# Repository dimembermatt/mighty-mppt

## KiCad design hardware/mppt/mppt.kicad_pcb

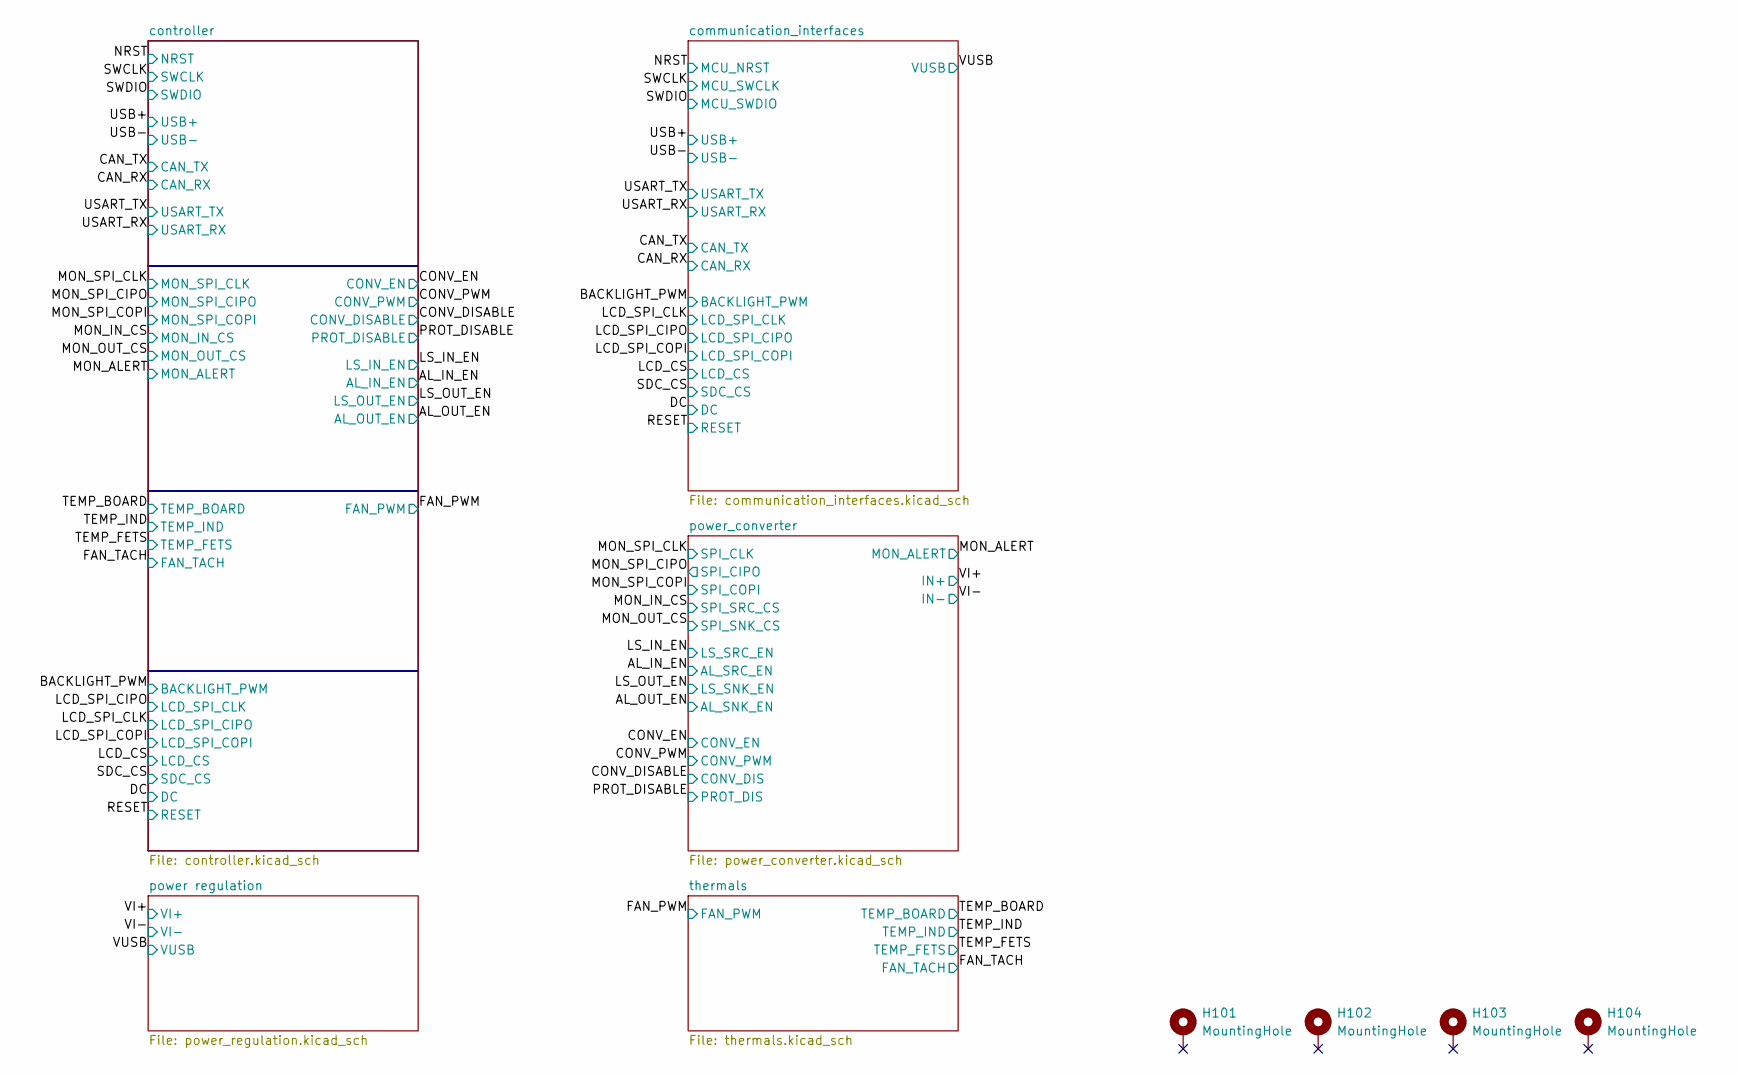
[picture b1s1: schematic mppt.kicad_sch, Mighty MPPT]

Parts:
H101, H102, H103, H104: MountingHole; MountingHole_2.7mm_M2.5_DIN965_Pad_TopBottom

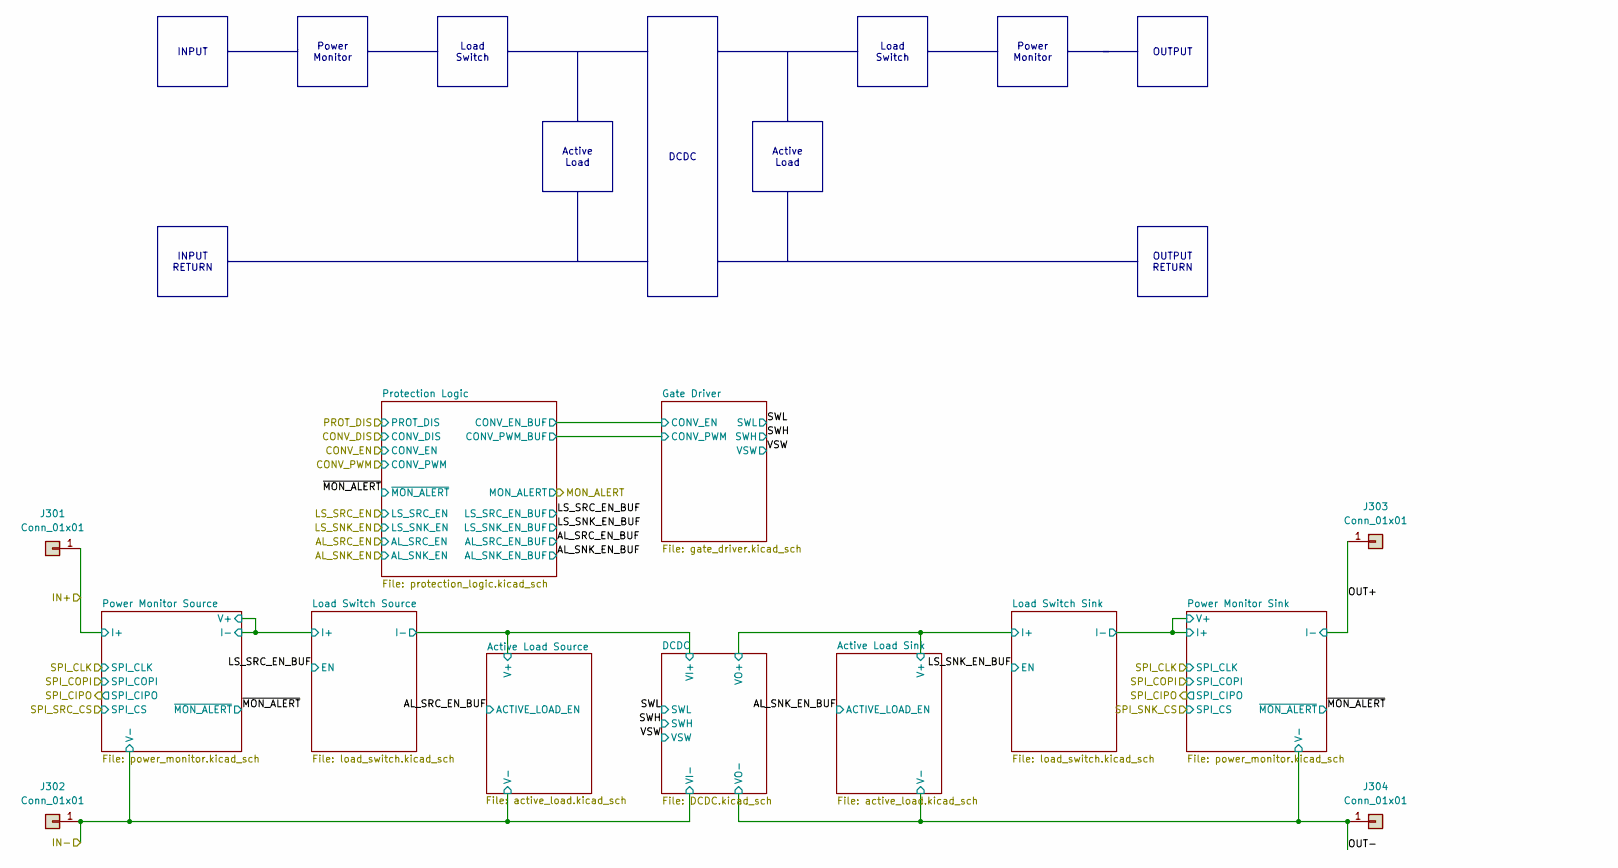
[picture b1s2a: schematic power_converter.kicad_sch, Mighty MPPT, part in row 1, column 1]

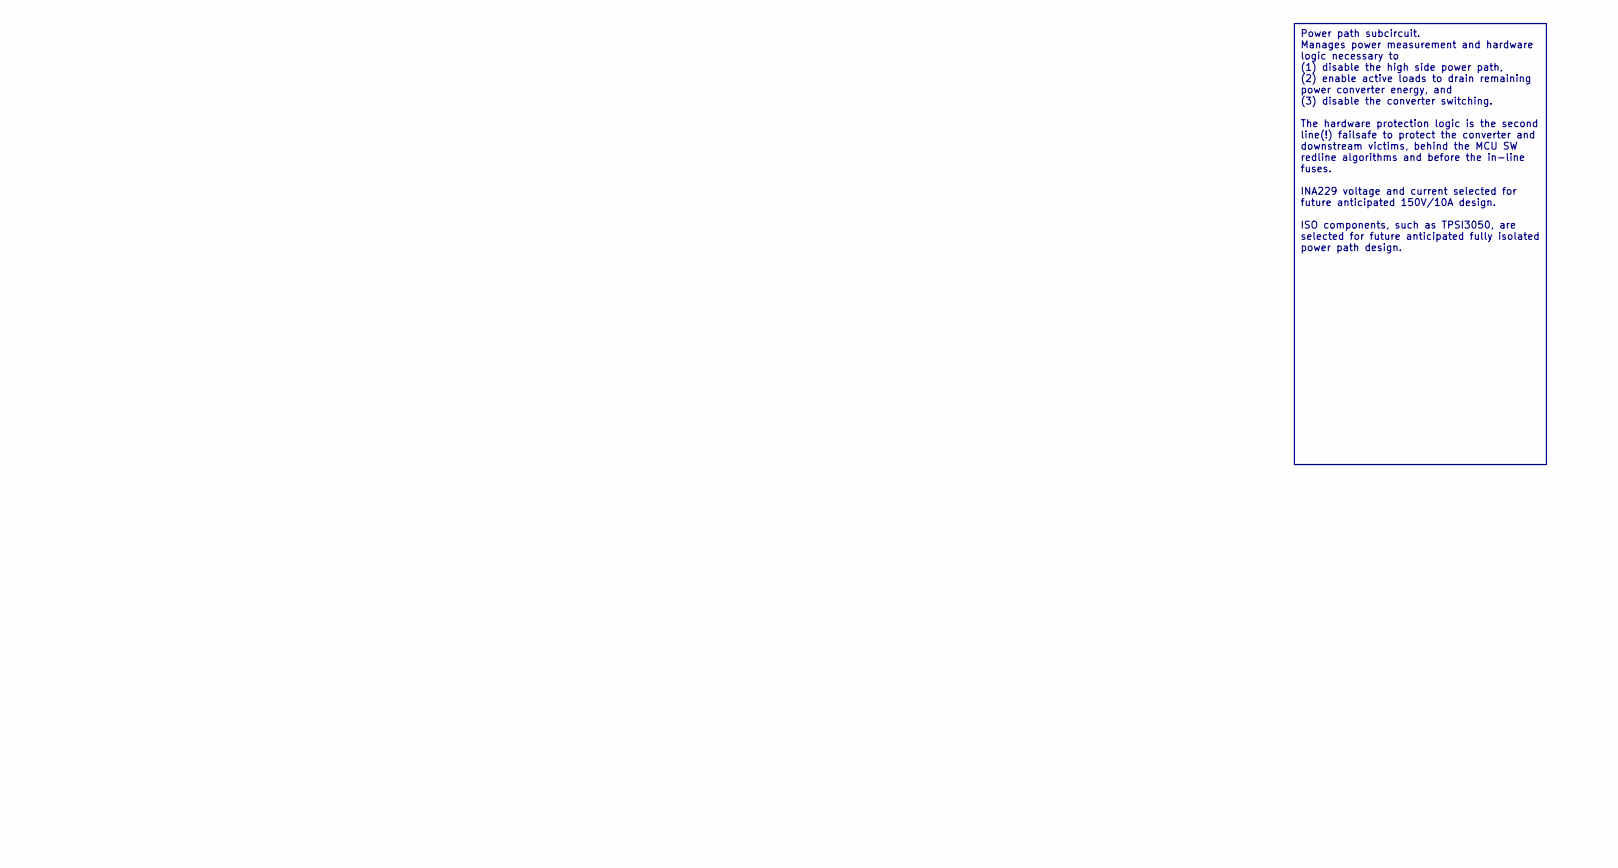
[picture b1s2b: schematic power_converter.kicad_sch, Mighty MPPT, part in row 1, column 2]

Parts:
J301, J302, J303, J304: Conn_01x01; ke_7771_SEMS

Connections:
/VI+: J301.1; also elsewhere on the board
/VI-: J302.1; also elsewhere on the board
/power_converter/OUT+: J303.1; also elsewhere on the board
/power_converter/OUT-: J304.1; also elsewhere on the board

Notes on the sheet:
INPUT
OUTPUT
Power Monitor
OUTPUT RETURN
DCDC
Power Monitor
Power path subcircuit. Manages power measurement and hardware logic necessary to (1) disable the high side power path, (2) enable active loads to drain remaining power converter energy, and (3) disable the converter switching. The hardware protection logic is the second line(!) failsafe to protect 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
Active Load
INPUT RETURN
Load Switch

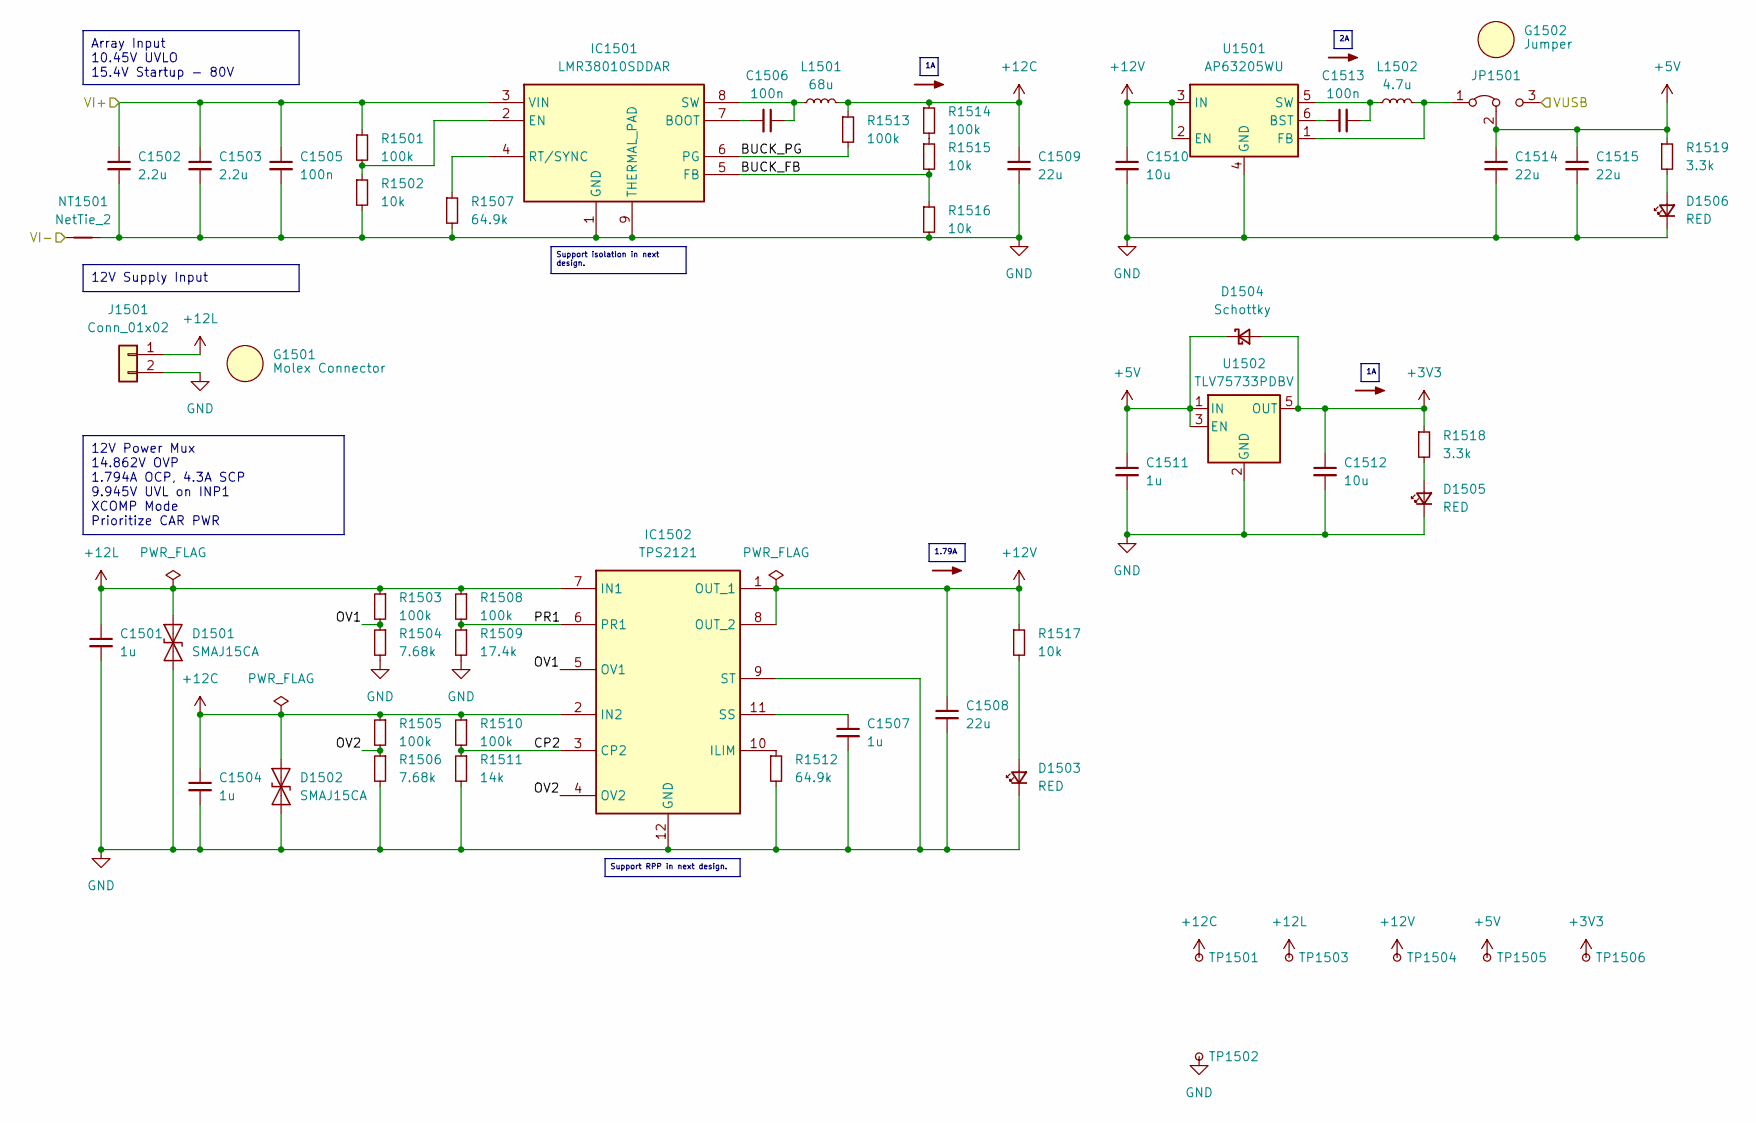
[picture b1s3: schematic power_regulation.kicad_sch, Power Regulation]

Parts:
C1501, C1504, C1507, C1511: 1u; C_0603_1608Metric_Pad1.08x0.95mm_HandSolder
C1502, C1503: 2.2u; C_2220_5750Metric
C1505: 100n; C_0805_2012Metric
C1506, C1513: 100n; C_0402_1005Metric_Pad0.74x0.62mm_HandSolder
C1508, C1509, C1514, C1515: 22u; C_1206_3216Metric
C1510, C1512: 10u; C_1206_3216Metric_Pad1.33x1.80mm_HandSolder
D1501, D1502: SMAJ15CA; D_SMA
D1503, D1505, D1506: RED; LED_0805_2012Metric_Pad1.15x1.40mm_HandSolder
D1504: Schottky; D_SOD-123F
G1501: Molex Connector
G1502: Jumper
IC1501: LMR38010SDDAR; ti_LMR38010_SDDAR
IC1502: TPS2121; ti_TPS2121_RUXR
J1501: Conn_01x02; Molex_Micro-Fit_3.0_43650-0215_1x02_P3.00mm_Vertical
JP1501: Jumper_3_Bridged12; PinSocket_1x03_P2.54mm_Vertical
L1501: 68u; L_Bourns_SRN6045TA
L1502: 4.7u; L_Bourns_SRN6045TA
NT1501: NetTie_2; NetTie-2_SMD_Pad2.0mm
R1501, R1503, R1505, R1508, R1510, R1513, R1514: 100k; R_0603_1608Metric_Pad0.98x0.95mm_HandSolder
R1502, R1515, R1516, R1517: 10k; R_0603_1608Metric_Pad0.98x0.95mm_HandSolder
R1504, R1506: 7.68k; R_0603_1608Metric_Pad0.98x0.95mm_HandSolder
R1507, R1512: 64.9k; R_0603_1608Metric_Pad0.98x0.95mm_HandSolder
R1509: 17.4k; R_0603_1608Metric_Pad0.98x0.95mm_HandSolder
R1511: 14k; R_0603_1608Metric_Pad0.98x0.95mm_HandSolder
R1518, R1519: 3.3k; R_0603_1608Metric_Pad0.98x0.95mm_HandSolder
TP1501, TP1502, TP1503, TP1504, TP1505, TP1506: TestPoint_Small; TestPoint_Pad_D1.0mm
U1501: AP63205WU; TSOT-23-6
U1502: TLV75733PDBV; SOT-23-5

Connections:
+3V3: C1512.1, D1504.2 (A), R1518.1, TP1506.1, U1502.5 (OUT); also elsewhere on the board
+5V: C1511.1, C1514.1, C1515.1, D1504.1 (K), JP1501.2 (C), R1519.1, TP1505.1, U1502.1 (IN), U1502.3 (EN); also elsewhere on the board
+12C: C1504.1, C1509.1, D1502.2 (A2), IC1502.2 (IN2), L1501.2, R1505.1, R1510.1, R1513.1, R1514.1, TP1501.1
+12L: C1501.1, D1501.2 (A2), IC1502.7 (IN1), J1501.1, R1503.1, R1508.1, TP1503.1
+12V: C1508.1, C1510.1, IC1502.1 (OUT_1), IC1502.8 (OUT_2), R1517.1, TP1504.1, U1501.2 (EN), U1501.3 (IN)
/VI+: C1502.1, C1503.1, C1505.1, IC1501.3 (VIN), R1501.1; also elsewhere on the board
/VI-: NT1501.2; also elsewhere on the board
/VUSB: JP1501.3 (B); also elsewhere on the board
/power regulation/BUCK_FB: IC1501.5 (FB), R1515.2, R1516.1
/power regulation/BUCK_PG: IC1501.6 (PG), R1513.2
/power regulation/CP2: IC1502.3 (CP2), R1510.2, R1511.1
/power regulation/OV1: IC1502.5 (OV1), R1503.2, R1504.1
/power regulation/OV2: IC1502.4 (OV2), R1505.2, R1506.1
/power regulation/PR1: IC1502.6 (PR1), R1508.2, R1509.1
GND: C1501.2, C1502.2, C1503.2, C1504.2, C1505.2, C1507.2, C1508.2, C1509.2, C1510.2, C1511.2, C1512.2, C1514.2, C1515.2, D1501.1 (A1), D1502.1 (A1), D1503.1 (K), D1505.1 (K), D1506.1 (K), IC1501.1 (GND), IC1501.9 (THERMAL_PAD), IC1502.9 (ST), IC1502.12 (GND), J1501.2, NT1501.1, R1502.2, R1504.2, R1506.2, R1507.2, R1509.2, R1511.2, R1512.2, R1516.2, TP1502.1, U1501.4 (GND), U1502.2 (GND); also elsewhere on the board
unnamed: D1503.2 (A), R1517.2
unnamed: D1505.2 (A), R1518.2
unnamed: D1506.2 (A), R1519.2
unnamed: C1506.2, IC1501.7 (BOOT)
unnamed: IC1501.2 (EN), R1501.2, R1502.1
unnamed: IC1501.4 (RT/SYNC), R1507.1
unnamed: C1506.1, IC1501.8 (SW), L1501.1
unnamed: IC1502.10 (ILIM), R1512.1
unnamed: C1507.1, IC1502.11 (SS)
unnamed: JP1501.1 (A), L1502.2, U1501.1 (FB)
unnamed: R1514.2, R1515.1
unnamed: C1513.1, U1501.6 (BST)
unnamed: C1513.2, L1502.1, U1501.5 (SW)

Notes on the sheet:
1.79A
Support isolation in next design.
12V Supply Input
12V Power Mux 14.862V OVP 1.794A OCP, 4.3A SCP 9.945V UVL on INP1 XCOMP Mode Prioritize CAR PWR
Array Input 10.45V UVLO 15.4V Startup - 80V
Support RPP in next design.

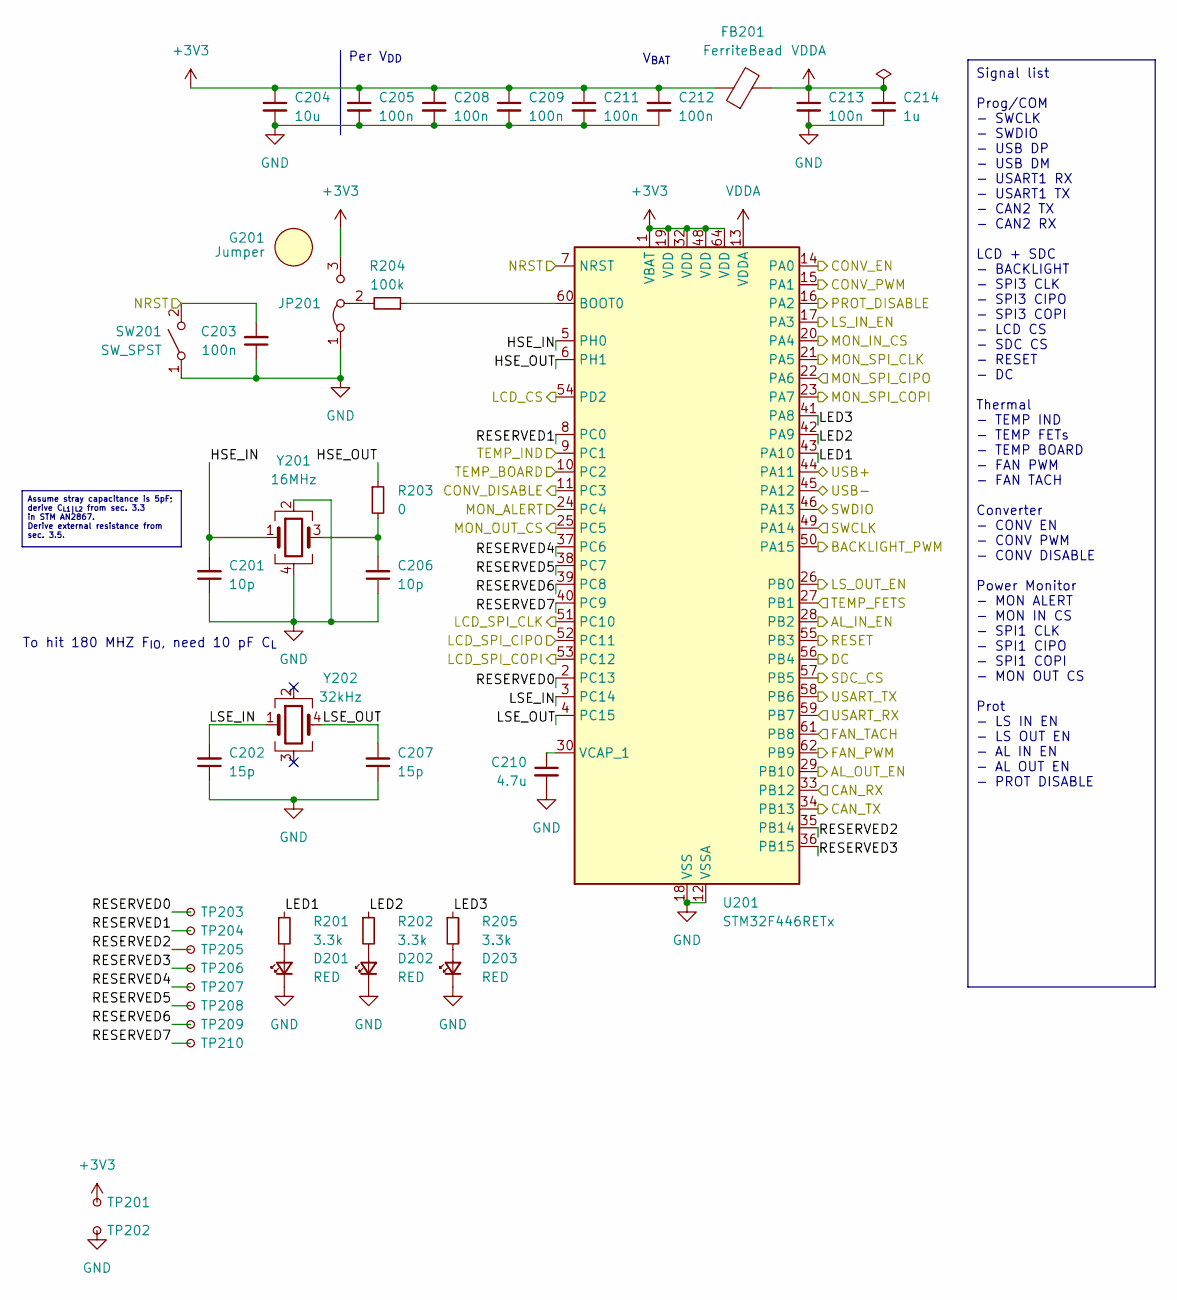
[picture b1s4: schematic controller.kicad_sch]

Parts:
C201, C206: 10p; C_0402_1005Metric
C202, C207: 15p; C_0402_1005Metric
C203, C205, C208, C209, C211, C212, C213: 100n; C_0402_1005Metric_Pad0.74x0.62mm_HandSolder
C204: 10u; C_1206_3216Metric_Pad1.33x1.80mm_HandSolder
C210: 4.7u; C_0603_1608Metric
C214: 1u; C_0603_1608Metric_Pad1.08x0.95mm_HandSolder
D201, D202, D203: RED; LED_0805_2012Metric_Pad1.15x1.40mm_HandSolder
FB201: FerriteBead; R_0603_1608Metric_Pad0.98x0.95mm_HandSolder
G201: Jumper
JP201: Jumper_3_Bridged12; PinSocket_1x03_P2.54mm_Vertical
R201, R202, R205: 3.3k; R_0603_1608Metric_Pad0.98x0.95mm_HandSolder
R203: 0; R_0805_2012Metric_Pad1.20x1.40mm_HandSolder
R204: 100k; R_0603_1608Metric_Pad0.98x0.95mm_HandSolder
SW201: SW_SPST; SW_PUSH_6mm
TP201, TP202, TP203, TP204, TP205, TP206, TP207, TP208, TP209, TP210: TestPoint_Small; TestPoint_Pad_D1.0mm
U201: STM32F446RETx; LQFP-64_10x10mm_P0.5mm
Y201: 16MHz; Crystal_SMD_Abracon_ABM8G-4Pin_3.2x2.5mm
Y202: 32kHz; Crystal_SMD_Abracon_ABS25-4Pin_8.0x3.8mm

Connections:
+3V3: C204.1, C205.1, C208.1, C209.1, C211.1, C212.1, FB201.1, JP201.3 (B), TP201.1, U201.1 (VBAT), U201.19 (VDD), U201.32 (VDD), U201.48 (VDD), U201.64 (VDD); also elsewhere on the board
/AL_IN_EN: U201.28 (PB2); also elsewhere on the board
/AL_OUT_EN: U201.29 (PB10); also elsewhere on the board
/BACKLIGHT_PWM: U201.50 (PA15); also elsewhere on the board
/CAN_RX: U201.33 (PB12); also elsewhere on the board
/CAN_TX: U201.34 (PB13); also elsewhere on the board
/CONV_DISABLE: U201.11 (PC3); also elsewhere on the board
/CONV_EN: U201.14 (PA0); also elsewhere on the board
/CONV_PWM: U201.15 (PA1); also elsewhere on the board
/DC: U201.56 (PB4); also elsewhere on the board
/FAN_PWM: U201.62 (PB9); also elsewhere on the board
/FAN_TACH: U201.61 (PB8); also elsewhere on the board
/LCD_CS: U201.54 (PD2); also elsewhere on the board
/LCD_SPI_CIPO: U201.51 (PC10); also elsewhere on the board
/LCD_SPI_CLK: U201.52 (PC11); also elsewhere on the board
/LCD_SPI_COPI: U201.53 (PC12); also elsewhere on the board
/LS_IN_EN: U201.17 (PA3); also elsewhere on the board
/LS_OUT_EN: U201.26 (PB0); also elsewhere on the board
/MON_ALERT: U201.24 (PC4); also elsewhere on the board
/MON_IN_CS: U201.20 (PA4); also elsewhere on the board
/MON_OUT_CS: U201.25 (PC5); also elsewhere on the board
/MON_SPI_CIPO: U201.22 (PA6); also elsewhere on the board
/MON_SPI_CLK: U201.21 (PA5); also elsewhere on the board
/MON_SPI_COPI: U201.23 (PA7); also elsewhere on the board
/NRST: C203.2, SW201.2 (B), U201.7 (NRST); also elsewhere on the board
/PROT_DISABLE: U201.16 (PA2); also elsewhere on the board
/RESET: U201.55 (PB3); also elsewhere on the board
/SDC_CS: U201.57 (PB5); also elsewhere on the board
/SWCLK: U201.49 (PA14); also elsewhere on the board
/SWDIO: U201.46 (PA13); also elsewhere on the board
/TEMP_BOARD: U201.10 (PC2); also elsewhere on the board
/TEMP_FETS: U201.27 (PB1); also elsewhere on the board
/TEMP_IND: U201.9 (PC1); also elsewhere on the board
/USART_RX: U201.59 (PB7); also elsewhere on the board
/USART_TX: U201.58 (PB6); also elsewhere on the board
/USB+: U201.44 (PA11); also elsewhere on the board
/USB-: U201.45 (PA12); also elsewhere on the board
/controller/HSE_IN: C201.2, U201.5 (PH0), Y201.1
/controller/HSE_OUT: R203.1, U201.6 (PH1)
/controller/LED1: R201.1, U201.43 (PA10)
/controller/LED2: R202.1, U201.42 (PA9)
/controller/LED3: R205.1, U201.41 (PA8)
/controller/LSE_IN: C202.2, U201.3 (PC14), Y202.1
/controller/LSE_OUT: C207.2, U201.4 (PC15), Y202.4
/controller/RESERVED0: TP203.1, U201.2 (PC13)
/controller/RESERVED1: TP204.1, U201.8 (PC0)
/controller/RESERVED2: TP205.1, U201.35 (PB14)
/controller/RESERVED3: TP206.1, U201.36 (PB15)
/controller/RESERVED4: TP207.1, U201.37 (PC6)
/controller/RESERVED5: TP208.1, U201.38 (PC7)
/controller/RESERVED6: TP209.1, U201.39 (PC8)
/controller/RESERVED7: TP210.1, U201.40 (PC9)
GND: C201.1, C202.1, C203.1, C204.2, C205.2, C206.1, C207.1, C208.2, C209.2, C210.2, C211.2, C212.2, C213.2, C214.2, D201.1 (K), D202.1 (K), D203.1 (K), JP201.1 (A), SW201.1 (A), TP202.1, U201.12 (VSSA), U201.18 (VSS), U201.31 (VSS), U201.47 (VSS), U201.63 (VSS), Y201.2, Y201.4; also elsewhere on the board
unnamed: C206.2, R203.2, Y201.3
unnamed: D201.2 (A), R201.2
unnamed: D202.2 (A), R202.2
unnamed: D203.2 (A), R205.2
unnamed: JP201.2 (C), R204.2
unnamed: R204.1, U201.60 (BOOT0)
unnamed: C210.1, U201.30 (VCAP_1)
VDDA: C213.1, C214.1, FB201.2, U201.13 (VDDA)

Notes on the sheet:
Assume stray capacitance is 5pF; derive C_{L1|L2} from sec. 3.3 in STM AN2867. Derive external resistance from sec. 3.5.
Signal list Prog/COM - SWCLK - SWDIO - USB DP - USB DM - USART1 RX - USART1 TX - CAN2 TX - CAN2 RX LCD + SDC - BACKLIGHT - SPI3 CLK - SPI3 CIPO - SPI3 COPI - LCD CS - SDC CS - RESET - DC Thermal - TEMP IND - TEMP FETs - TEMP BOARD - FAN PWM - FAN TACH Converter - CONV EN - CONV PWM - CONV DISABLE P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
To hit 180 MHZ F_{IO}, need 10 pF C_{L}
Per V_{DD}
V_{BAT}

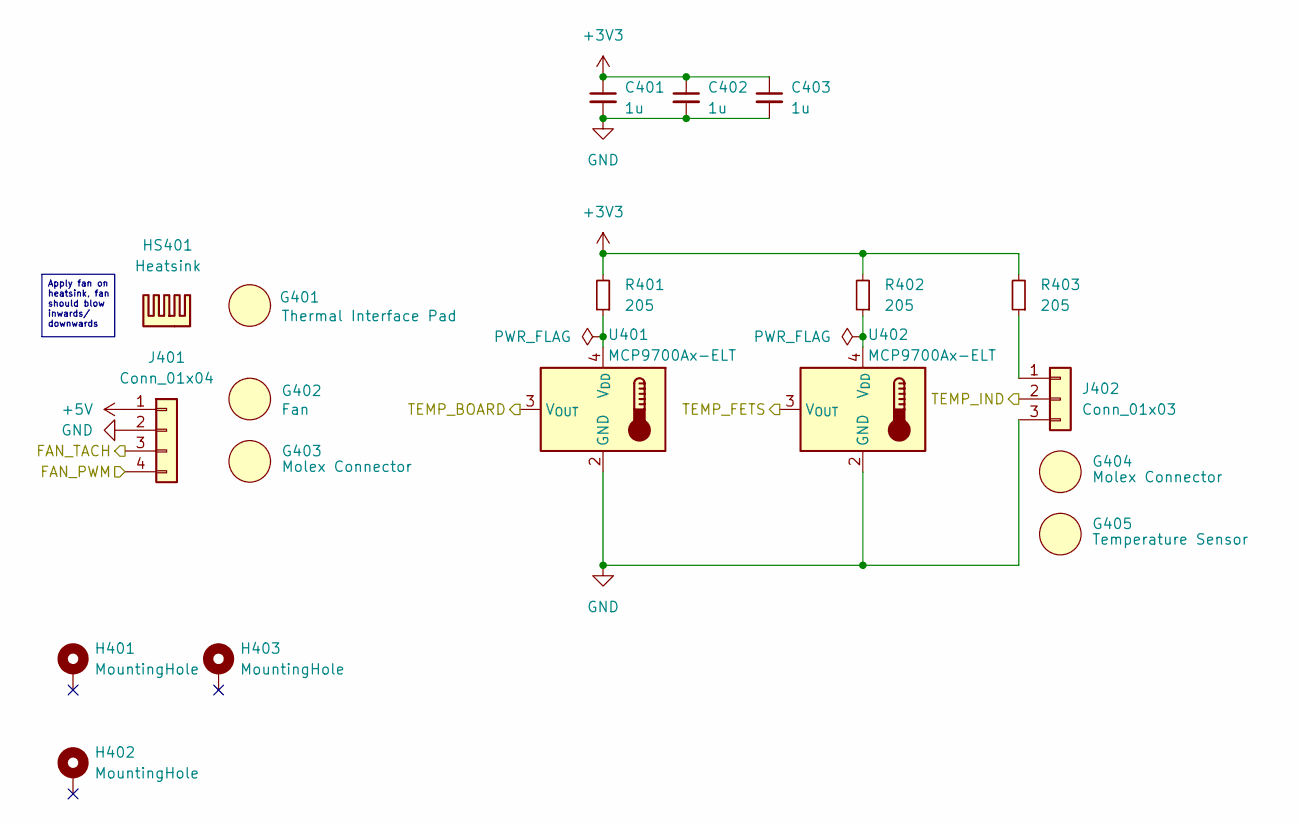
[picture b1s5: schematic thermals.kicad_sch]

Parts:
C401, C402, C403: 1u; C_0603_1608Metric_Pad1.08x0.95mm_HandSolder
G401: Thermal Interface Pad
G402: Fan
G403, G404: Molex Connector
G405: Temperature Sensor
H401, H402, H403: MountingHole; MountingHole_2.2mm_M2_DIN965_Pad_TopBottom
HS401: Heatsink
J401: Conn_01x04; Molex_Micro-Fit_3.0_43650-0415_1x04_P3.00mm_Vertical
J402: Conn_01x03; Molex_Micro-Fit_3.0_43650-0315_1x03_P3.00mm_Vertical
R401, R402, R403: 205; R_0603_1608Metric_Pad0.98x0.95mm_HandSolder
U401, U402: MCP9700Ax-ELT; SOT-353_SC-70-5

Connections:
+3V3: C401.1, C402.1, C403.1, R401.2, R402.2, R403.2; also elsewhere on the board
+5V: J401.1; also elsewhere on the board
/FAN_PWM: J401.4; also elsewhere on the board
/FAN_TACH: J401.3; also elsewhere on the board
/TEMP_BOARD: U401.3 (V_{OUT}); also elsewhere on the board
/TEMP_FETS: U402.3 (V_{OUT}); also elsewhere on the board
/TEMP_IND: J402.2; also elsewhere on the board
GND: C401.2, C402.2, C403.2, J401.2, J402.3, U401.2 (GND), U402.2 (GND); also elsewhere on the board
unnamed: J402.1, R403.1
unnamed: R401.1, U401.4 (V_{DD})
unnamed: R402.1, U402.4 (V_{DD})

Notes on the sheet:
Apply fan on heatsink, fan should blow inwards/ downwards

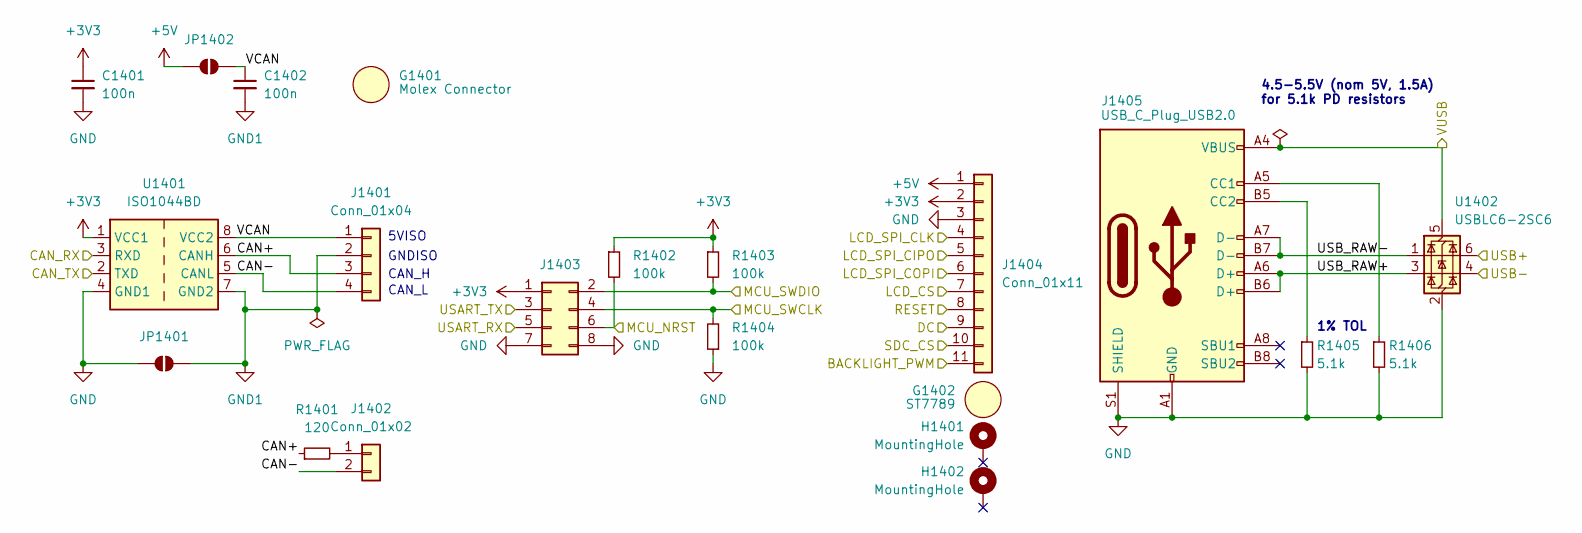
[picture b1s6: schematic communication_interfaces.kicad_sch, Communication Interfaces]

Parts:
C1401, C1402: 100n; C_0402_1005Metric_Pad0.74x0.62mm_HandSolder
G1401: Molex Connector
G1402: ST7789
H1401, H1402: MountingHole; MountingHole_2.7mm_M2.5_DIN965_Pad_TopBottom
J1401: Conn_01x04; Molex_Micro-Fit_3.0_43650-0415_1x04_P3.00mm_Vertical
J1402: Conn_01x02; PinHeader_1x02_P2.54mm_Vertical
J1403: Conn_02x04_Odd_Even; PinHeader_2x04_P2.54mm_Vertical
J1404: Conn_01x11; PinHeader_1x11_P2.54mm_Vertical
J1405: USB_C_Plug_USB2.0; USB_C_Receptacle_GCT_USB4105-xx-A_16P_TopMnt_Horizontal
JP1401, JP1402: SolderJumper_2_Open; SolderJumper-2_P1.3mm_Open_TrianglePad1.0x1.5mm
R1401: 120; R_0603_1608Metric_Pad0.98x0.95mm_HandSolder
R1402, R1403, R1404: 100k; R_0603_1608Metric_Pad0.98x0.95mm_HandSolder
R1405, R1406: 5.1k; R_0603_1608Metric_Pad0.98x0.95mm_HandSolder
U1401: ISO1044BD; SOIC-8_3.9x4.9mm_P1.27mm
U1402: USBLC6-2SC6; SOT-23-6

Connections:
+3V3: C1401.1, J1403.1, J1404.2, R1402.1, R1403.1, U1401.1 (VCC1); also elsewhere on the board
+5V: J1404.1, JP1402.1 (A); also elsewhere on the board
/BACKLIGHT_PWM: J1404.11; also elsewhere on the board
/CAN_RX: U1401.3 (RXD); also elsewhere on the board
/CAN_TX: U1401.2 (TXD); also elsewhere on the board
/DC: J1404.9; also elsewhere on the board
/LCD_CS: J1404.7; also elsewhere on the board
/LCD_SPI_CIPO: J1404.5; also elsewhere on the board
/LCD_SPI_CLK: J1404.4; also elsewhere on the board
/LCD_SPI_COPI: J1404.6; also elsewhere on the board
/NRST: J1403.6, R1402.2; also elsewhere on the board
/RESET: J1404.8; also elsewhere on the board
/SDC_CS: J1404.10; also elsewhere on the board
/SWCLK: J1403.4, R1404.2; also elsewhere on the board
/SWDIO: J1403.2, R1403.2; also elsewhere on the board
/USART_RX: J1403.5; also elsewhere on the board
/USART_TX: J1403.3; also elsewhere on the board
/USB+: U1402.6 (I/O1); also elsewhere on the board
/USB-: U1402.4 (I/O2); also elsewhere on the board
/VUSB: J1405.A4 (VBUS), J1405.A9 (VBUS), J1405.B4 (VBUS), J1405.B9 (VBUS), U1402.5 (VBUS); also elsewhere on the board
/communication_interfaces/CAN+: J1401.3, R1401.1, U1401.6 (CANH)
/communication_interfaces/CAN-: J1401.4, J1402.2, U1401.5 (CANL)
/communication_interfaces/USB_RAW+: J1405.A6 (D+), J1405.B6 (D+), U1402.3 (I/O2)
/communication_interfaces/USB_RAW-: J1405.A7 (D-), J1405.B7 (D-), U1402.1 (I/O1)
/communication_interfaces/VCAN: C1402.1, J1401.1, JP1402.2 (B), U1401.8 (VCC2)
GND: C1401.2, J1403.7, J1403.8, J1404.3, J1405.A1 (GND), J1405.A12 (GND), J1405.B1 (GND), J1405.B12 (GND), J1405.S1 (SHIELD), JP1401.1 (A), R1404.1, R1405.2, R1406.2, U1401.4 (GND1), U1402.2 (GND); also elsewhere on the board
GND1: C1402.2, J1401.2, JP1401.2 (B), U1401.7 (GND2)
unnamed: J1402.1, R1401.2
unnamed: J1405.A5 (CC1), R1406.1
unnamed: J1405.B5 (CC2), R1405.1

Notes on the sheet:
1% TOL
CAN_H
GNDISO
4.5-5.5V (nom 5V, 1.5A) for 5.1k PD resistors
CAN_L
5VISO

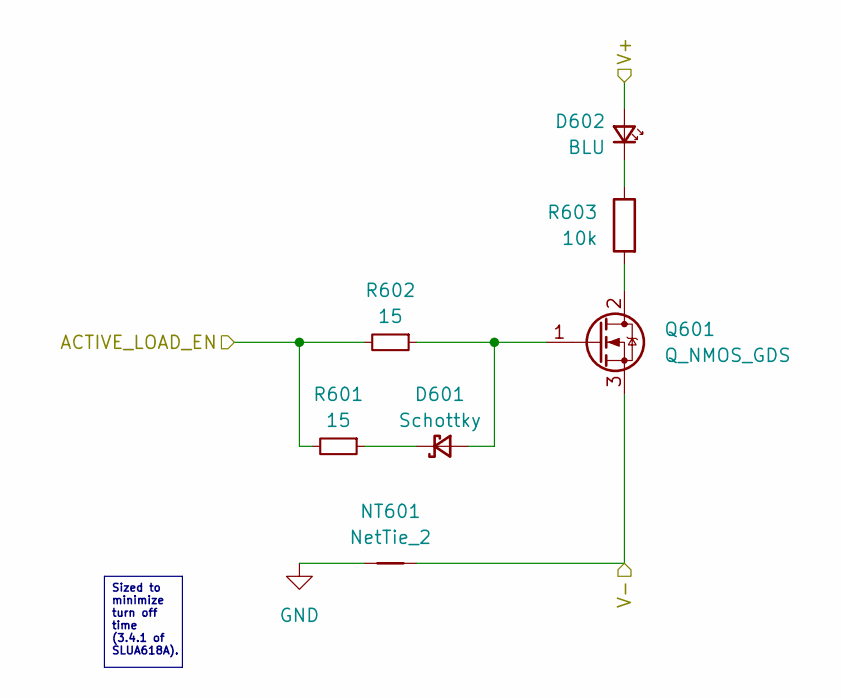
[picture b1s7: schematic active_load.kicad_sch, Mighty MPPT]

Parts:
D601: Schottky; D_SOD-123F
D602: BLU; LED_0805_2012Metric_Pad1.15x1.40mm_HandSolder
NT601: NetTie_2; NetTie-2_SMD_Pad0.5mm
Q601: Q_NMOS_GDS; SOT-223-3_TabPin2
R601, R602: 15; R_0603_1608Metric
R603: 10k; R_2512_6332Metric_Pad1.40x3.35mm_HandSolder

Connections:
/power_converter/AL_SNK_EN_BUF: R601.2, R602.2; also elsewhere on the board
/power_converter/Active Load Sink/V+: D602.2 (A); also elsewhere on the board
/power_converter/OUT-: NT601.2, Q601.3 (S); also elsewhere on the board
GND: NT601.1; also elsewhere on the board
unnamed: D601.2 (A), Q601.1 (G), R602.1
unnamed: D601.1 (K), R601.1
unnamed: D602.1 (K), R603.1
unnamed: Q601.2 (D), R603.2

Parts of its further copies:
D701: Schottky; D_SOD-123F
D702: BLU; LED_0805_2012Metric_Pad1.15x1.40mm_HandSolder
NT701: NetTie_2; NetTie-2_SMD_Pad0.5mm
Q701: Q_NMOS_GDS; SOT-223-3_TabPin2
R701, R702: 15; R_0603_1608Metric
R703: 10k; R_2512_6332Metric_Pad1.40x3.35mm_HandSolder

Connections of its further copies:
/VI-: NT701.2, Q701.3 (S); also elsewhere on the board
/power_converter/AL_SRC_EN_BUF: R701.2, R702.2; also elsewhere on the board
/power_converter/Active Load Source/V+: D702.2 (A); also elsewhere on the board
GND: NT701.1; also elsewhere on the board
unnamed: D701.2 (A), Q701.1 (G), R702.1
unnamed: D701.1 (K), R701.1
unnamed: D702.1 (K), R703.1
unnamed: Q701.2 (D), R703.2

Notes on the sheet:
Sized to minimize turn off time (3.4.1 of SLUA618A).

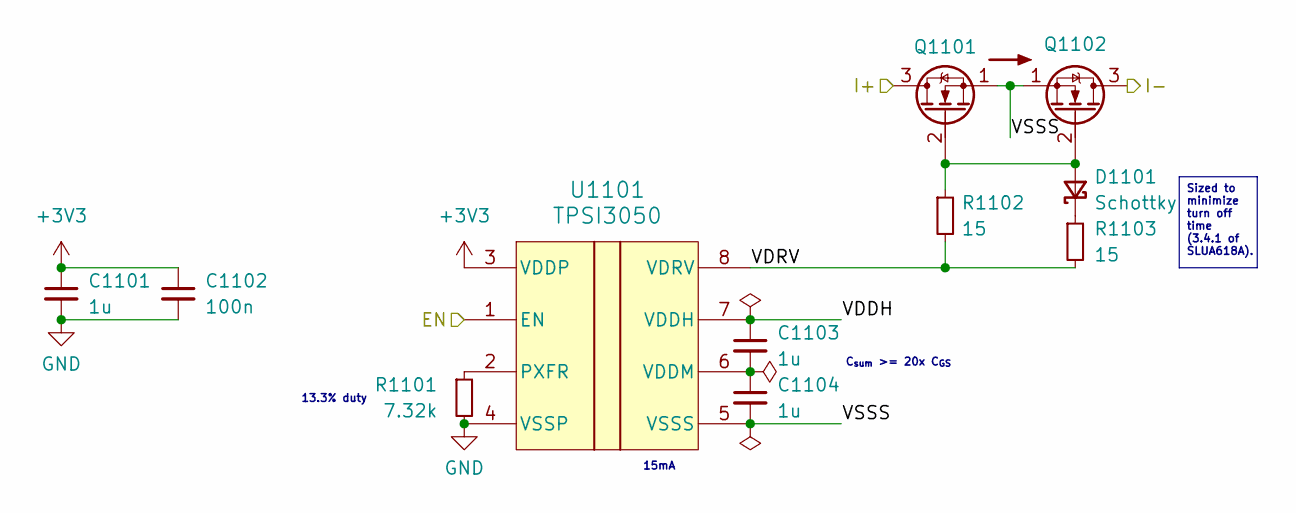
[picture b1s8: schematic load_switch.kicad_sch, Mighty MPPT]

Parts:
C1101, C1103, C1104: 1u; C_0603_1608Metric_Pad1.08x0.95mm_HandSolder
C1102: 100n; C_0402_1005Metric_Pad0.74x0.62mm_HandSolder
D1101: Schottky; D_SOD-123F
Q1101, Q1102: Q_NMOS_SGD; PowerPAK_SO-8_Single
R1101: 7.32k; R_0603_1608Metric_Pad0.98x0.95mm_HandSolder
R1102, R1103: 15; R_0603_1608Metric
U1101: TPSI3050; ti_TPS3050_DWZ

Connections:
+3V3: C1101.1, C1102.1, U1101.3 (VDDP); also elsewhere on the board
/power_converter/Active Load Sink/V+: Q1101.3 (D); also elsewhere on the board
/power_converter/LS_SNK_EN_BUF: U1101.1 (EN); also elsewhere on the board
/power_converter/Load Switch Sink/I-: Q1102.3 (D); also elsewhere on the board
/power_converter/Load Switch Sink/VDDH: C1103.1, U1101.7 (VDDH)
/power_converter/Load Switch Sink/VDRV: R1102.2, R1103.2, U1101.8 (VDRV)
/power_converter/Load Switch Sink/VSSS: C1104.2, Q1101.1 (S), Q1102.1 (S), U1101.5 (VSSS)
GND: C1101.2, C1102.2, R1101.2, U1101.4 (VSSP); also elsewhere on the board
unnamed: D1101.2 (A), Q1101.2 (G), Q1102.2 (G), R1102.1
unnamed: D1101.1 (K), R1103.1
unnamed: R1101.1, U1101.2 (PXFR)
unnamed: C1103.2, C1104.1, U1101.6 (VDDM)

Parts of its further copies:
C1201, C1203, C1204: 1u; C_0603_1608Metric_Pad1.08x0.95mm_HandSolder
C1202: 100n; C_0402_1005Metric_Pad0.74x0.62mm_HandSolder
D1201: Schottky; D_SOD-123F
Q1201, Q1202: Q_NMOS_SGD; PowerPAK_SO-8_Single
R1201: 7.32k; R_0603_1608Metric_Pad0.98x0.95mm_HandSolder
R1202, R1203: 15; R_0603_1608Metric
U1201: TPSI3050; ti_TPS3050_DWZ

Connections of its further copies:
+3V3: C1201.1, C1202.1, U1201.3 (VDDP); also elsewhere on the board
/power_converter/Active Load Source/V+: Q1202.3 (D); also elsewhere on the board
/power_converter/LS_SRC_EN_BUF: U1201.1 (EN); also elsewhere on the board
/power_converter/Load Switch Source/I+: Q1201.3 (D); also elsewhere on the board
/power_converter/Load Switch Source/VDDH: C1203.1, U1201.7 (VDDH)
/power_converter/Load Switch Source/VDRV: R1202.2, R1203.2, U1201.8 (VDRV)
/power_converter/Load Switch Source/VSSS: C1204.2, Q1201.1 (S), Q1202.1 (S), U1201.5 (VSSS)
GND: C1201.2, C1202.2, R1201.2, U1201.4 (VSSP); also elsewhere on the board
unnamed: D1201.2 (A), Q1201.2 (G), Q1202.2 (G), R1202.1
unnamed: D1201.1 (K), R1203.1
unnamed: R1201.1, U1201.2 (PXFR)
unnamed: C1203.2, C1204.1, U1201.6 (VDDM)

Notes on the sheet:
Sized to minimize turn off time (3.4.1 of SLUA618A).
13.3% duty
15mA
C_{sum} >= 20x C_{GS}
